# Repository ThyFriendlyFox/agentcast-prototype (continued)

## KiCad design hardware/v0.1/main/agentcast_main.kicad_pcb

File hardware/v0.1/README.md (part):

# Agentcast dongle v0.1

> **Archived** at commit `2c0782a`. Superseded by [v0.2](../v0.2/) (one board).
> First version. Made from the spec in
> [`docs/office-agent-dongle.md`](../../docs/office-agent-dongle.md) with the
> [Via EE Workcenter](https://github.com/ThyFriendlyFox/via).

v0.1 is two boards joined by a 10-way cable:

| Board | Folder | Size | Layers | What it does |
|---|---|---|---|---|
| Main board | [`main/`](main/) | 66 x 52.2 mm | 4 | Carries a Raspberry Pi Compute Module 5. HDMI-A out to the TV, USB-C power and flashing, boot button, 2 LEDs, mic bar socket. |
| Mic bar | [`micbar/`](micbar/) | 140 x 14 mm | 2 | 4 I2S MEMS mics on one shared clock, hardware mute switch, LIVE / MUTED / STATE LEDs. |

| Main board | Mic bar, from above | Mic bar, from below (LEDs, mic ports) |
|---|---|---|
|  |  |  |
|  |  |  |

The pictures come from `workcenter render <board> --views all --spin-frames 36`;
the mic bar's view from below adds `--views spin --spin-frames 36 --spin-tilt -125`.
Default zoom and pivot; the 0, 90, 180 and 270 degree test frames were whole.
The CM5 sockets and the USB-C receptacle use box bodies from `main/models/`
(KiCad has none).

Schematics: [`main/docs/schematic.png`](main/docs/schematic.png),
[`micbar/docs/schematic.png`](micbar/docs/schematic.png).

## Gate results

`workcenter gates` on each board, at the commit that adds this file:

| Board | ERC | DRC | SIM | EXPORT |
|---|---|---|---|---|
| main | PASS, 0 errors, 0 warnings | PASS, 0 errors, 0 unconnected, 0 parity; 4 silk warnings (HDMI and USB-C shells cross the edge, as designed) | SKIP, no deck (see Open items) | PASS, 24 Gerber files, drill, BOM, PDF |
| micbar | PASS, 0 errors, 0 warnings | PASS, 0 errors, 0 unconnected, 0 parity; 2 silk warnings (switch actuator crosses the edge) | PASS, 1 deck (`mic_live`) | PASS, Gerbers, drill, BOM, PDF |

## How it maps to the spec

| Spec requirement | v0.1 answer |
|---|---|
| HDMI dongle, the TV shows only what the dongle sends | CM5 HDMI0 to an HDMI-A receptacle (J3). A short HDMI cable goes to the TV, like a Chromecast tail. |
| Small, cheap, the cloud does the work | A CM5 module does Wi-Fi, HDMI 2.0 and I2S. The carrier has 26 parts. |
| A separate power supply, not the TV's USB port | USB-C (J4). The CM5 negotiates 5 V up to 5 A on CC1/CC2 itself (CM5 datasheet 2.12.1). |
| Mic unit separate from the dongle body, on the TV, facing the room | The mic bar is its own board on a JST SH cable. |
| All mic channels, not one cleaned channel | 4 raw 24-bit channels on 2 I2S data lanes (I2S0_SDI[0], I2S0_SDI[1]). No DSP on the bar. |
| A fixed, known mic layout | 4 mics in a line, 40.0 mm pitch, 120 mm aperture, positions in `micbar/design.py`. |
| One shared clock | The CM5's I2S0 is the only clock master. All 4 mics take the same BCLK and WS. |
| A physical mute; the indicator tied to mic power | SW1 cuts the mics' supply. The green LIVE LED runs from that supply. The red MUTED LED runs from the switch's other throw. |
| Software cannot turn the mics on in secret | No GPIO can power the mics. The clock buffers also run from the switched supply, so muted mics cannot draw power through their clock pins. |
| People see the state from anywhere in the room | 3 LEDs on the bar's front face. The STATE LED is driven by the CM5 (GPIO6) for "waiting / active". |
| TV control over HDMI-CEC | HDMI pin 13 goes to the CM5's HDMI0_CEC. |
| Recovery without IT | A BOOT button (nRPIBOOT) and USB-C data for `rpiboot` flashing. |

Not in v0.1: wired Ethernet, a camera, a backup speaker, a fan, more than
4 mics. See Open items.

## Part choices

| Ref | Part | Why |
|---|---|---|
| main J1, J2 | Hirose DF40C-100DS-0.4V | The CM5 board-to-board sockets. 1.5 mm stack height (CM5 datasheet 4.1.1). |
| main J3 | Molex 208658-1001 HDMI-A, mid-mount | In KiCad's library; its PCB-edge mark sets the board edge. |
| main J4 | HRO TYPE-C-31-M-12 | Common 16-pin USB 2.0 receptacle. |
| main U1 | ST USBLC6-2SC6 | ESD on the USB D+/D- pair. |
| main F1, D1, C3 | 0.1 A PTC, BAT54WS, 100 nF | HDMI +5V (pin 18): limits a short, blocks back-feed from the TV. |
| main J5 / micbar J1 | JST SH SM10B-SRSS-TB | 10-way cable between the boards, same pinout both ends. |
| main R1, R2 | 33 ohm | Source termination for BCLK and WS on the cable. |
| main R3, R4, R5 | 100 k | Pull-downs: SD0, SD1 (tri-stated by the mics) and MIC_LIVE. |
| micbar MK1-MK4 | TDK InvenSense ICS-43434 | I2S output, 24-bit, bottom port. In KiCad's library. Two mics share one data line (L/R). |
| micbar U1, U2 | 74LVC1G34 | Clock buffers on the switched supply. LVC inputs have Ioff, so a powered clock into an unpowered buffer is safe. |
| micbar SW1 | C&K PCM12SMTR | Slide switch for mute, right-angle, out of the top edge. |
| micbar D1, D2, D3 | 0603 LEDs green, red, amber | LIVE, MUTED, STATE, on the front face (B.Cu). Amber for STATE: a white LED (Vf near 3 V) would not light reliably from a 3.3 V GPIO (VOH min 2.9 V, datasheet Table 8). |

KiCad has no CM5 symbol and no 2 x 50 generic connector, so
[`library/gen_library.py`](library/gen_library.py) writes `CM5_J1` and
`CM5_J2` from [`library/cm5_pins.csv`](library/cm5_pins.csv). The CSV was
parsed from the CM5 datasheet pinout table (section 4.2), all 200 pins.
The same script copies KiCad's ICS-43434 with SD as tri-state.

## Pin plan (CM5)

Read from the CM5 datasheet: the GPIO alternate-function table (section 2.9)
and the pinout (section 4.2). GPIO_VREF (pin 78) is tied to CM5_3.3V, so all
GPIO are 3.3 V.

| Signal | CM5 pin | GPIO | Function | Goes to |
|---|---|---|---|---|
| MIC_BCLK | 49 | GPIO18 | I2S0_SCLK (alt a2), master | R1, J5.3 |
| MIC_WS | 26 | GPIO19 | I2S0_WS (alt a2) | R2, J5.5 |
| MIC_SD0 | 27 | GPIO20 | I2S0_SDI[0] (alt a2) | J5.6, mics 1-2 |
| MIC_SD1 | 46 | GPIO22 | I2S0_SDI[1] (alt a2) | J5.7, mics 3-4 |
| MIC_LIVE | 34 | GPIO5 | input, high = mics powered | J5.8 |
| STATE_LED | 30 | GPIO6 | output, high = LED on, about 2.7 mA | J5.9 |
| LED_nACT | 21 | - | activity LED sink, 20 mA max | D3 |
| nRPIBOOT | 93 | - | boot from USB when low | SW1 |
| CC1 / CC2 | 94 / 96 | - | USB-C PD | J4 |
| USB_P / USB_N | 105 / 103 | - | USB 2.0 (OTG ID left open: device mode for rpiboot) | J4 via U1 |
| HDMI0 TX2/TX1/TX0/CLK | 170-190 (even) | - | TMDS | J3 pins 1-12 |
| HDMI0_CEC / HOTPLUG | 151 / 153 | - | 5 V tolerant, direct to the connector | J3.13 / J3.19 |
| HDMI0_SDA / SCL | 199 / 200 | - | 5 V tolerant, 1.8 k pull-ups inside the CM5 | J3.16 / J3.15 |
| 5V | 77-87 (odd) | - | 4.75-5.25 V in | In2.Cu +5V pour |
| CM5_3.3V | 84, 86 | - | out, 600 mA total | GPIO_VREF, mic bar |

Shared-resource checks: I2S0 is one block, so SDI[0] and SDI[1] share its
BCLK and WS by construction. GPIO18-22 have no second use on this board.
Nothing off the board reaches a GPIO but the cable; every cable signal is
powered from CM5_3.3V, which is off when the CM5 is off (datasheet 4.2.1,
"Reverse voltage").

## Mic bar cable (J5 on main, J1 on the bar)

| Pin | Net | Notes |
|---|---|---|
| 1 | +3V3 | CM5_3.3V to the mute switch |
| 2, 4, 10, MP | GND | |
| 3 | BCLK | 33 ohm at the CM5 end |
| 5 | WS | 33 ohm at the CM5 end |
| 6 | SD0 | mics 1 (L), 2 (R) |
| 7 | SD1 | mics 3 (L), 4 (R) |
| 8 | MIC_LIVE | 10 k from the mics' supply, 100 k pull-down on the main board |
| 9 | STATE_LED | CM5 GPIO6 to the amber LED through 330 ohm |

## External contacts

| Board | Contact | Position (board origin top-left) | Nets |
|---|---|---|---|
| main | J3 HDMI-A | bottom edge, centre x 17.45 mm | TMDS, CEC, DDC, HPD, +5VP, GND |
| main | J4 USB-C | bottom edge, centre x 48.0 mm | +5V, CC1, CC2, USB_DP, USB_DN, GND |
| main | J5 mic bar | right edge, centre y 20.0 mm | see the cable table |
| main | SW1 BOOT | x 32.0, y 47.5 mm | nRPIBOOT, GND |
| micbar | J1 cable | bottom edge, centre x 70.0 mm | see the cable table |
| micbar | SW1 mute | top edge, centre x 70.0 mm | +3V3, MIC_VDD, MUTED |
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
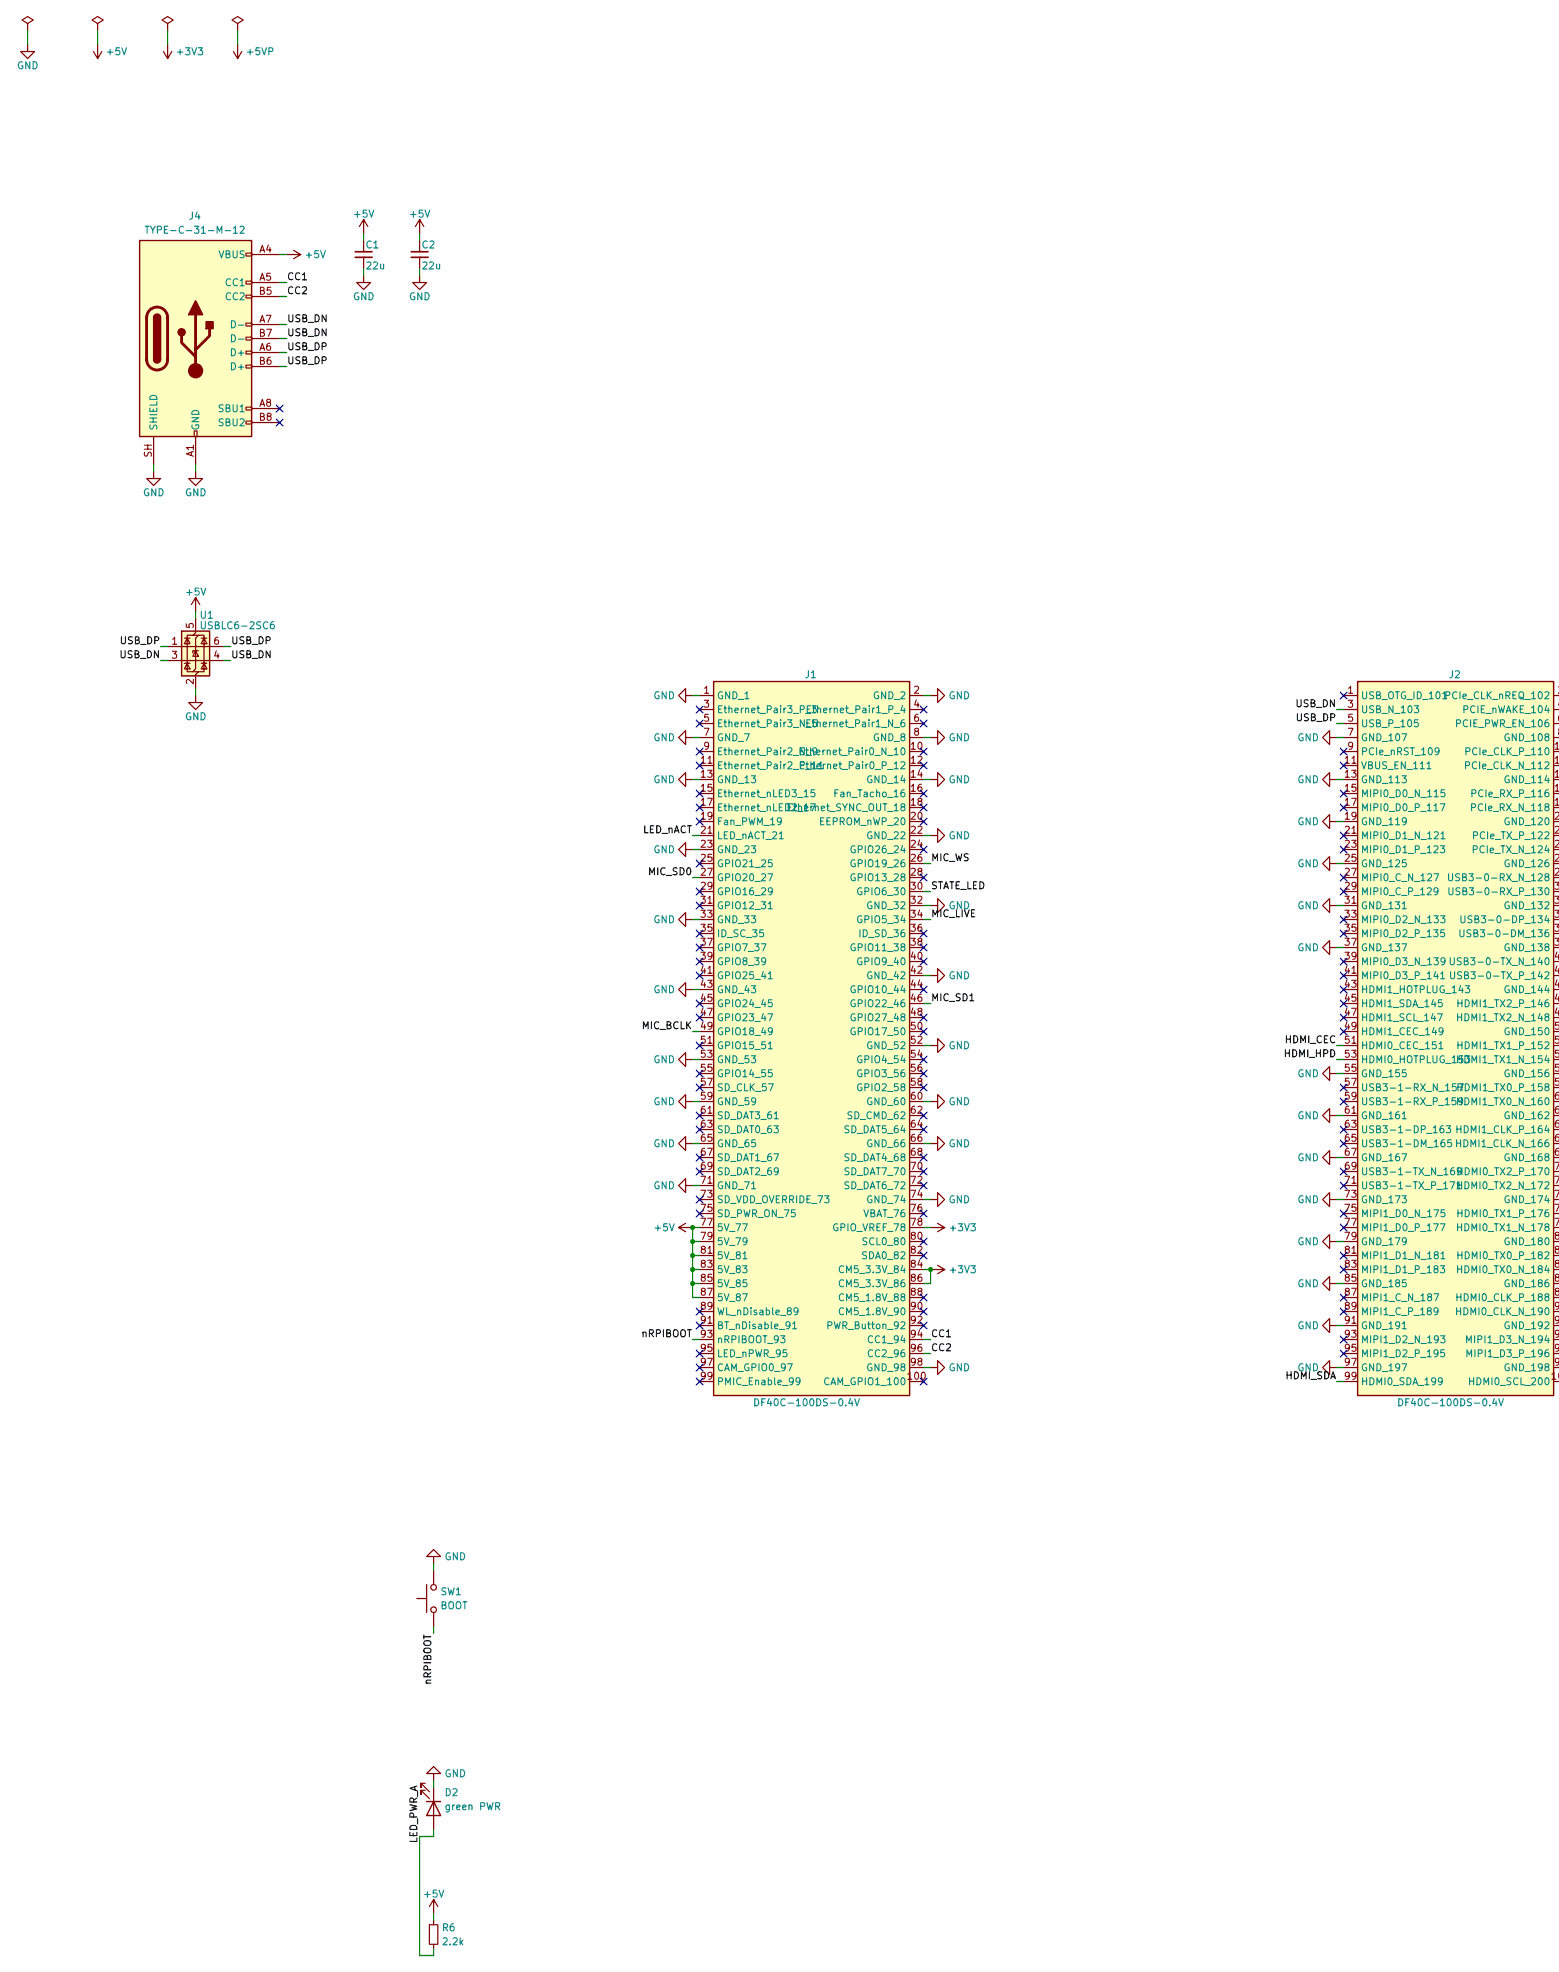
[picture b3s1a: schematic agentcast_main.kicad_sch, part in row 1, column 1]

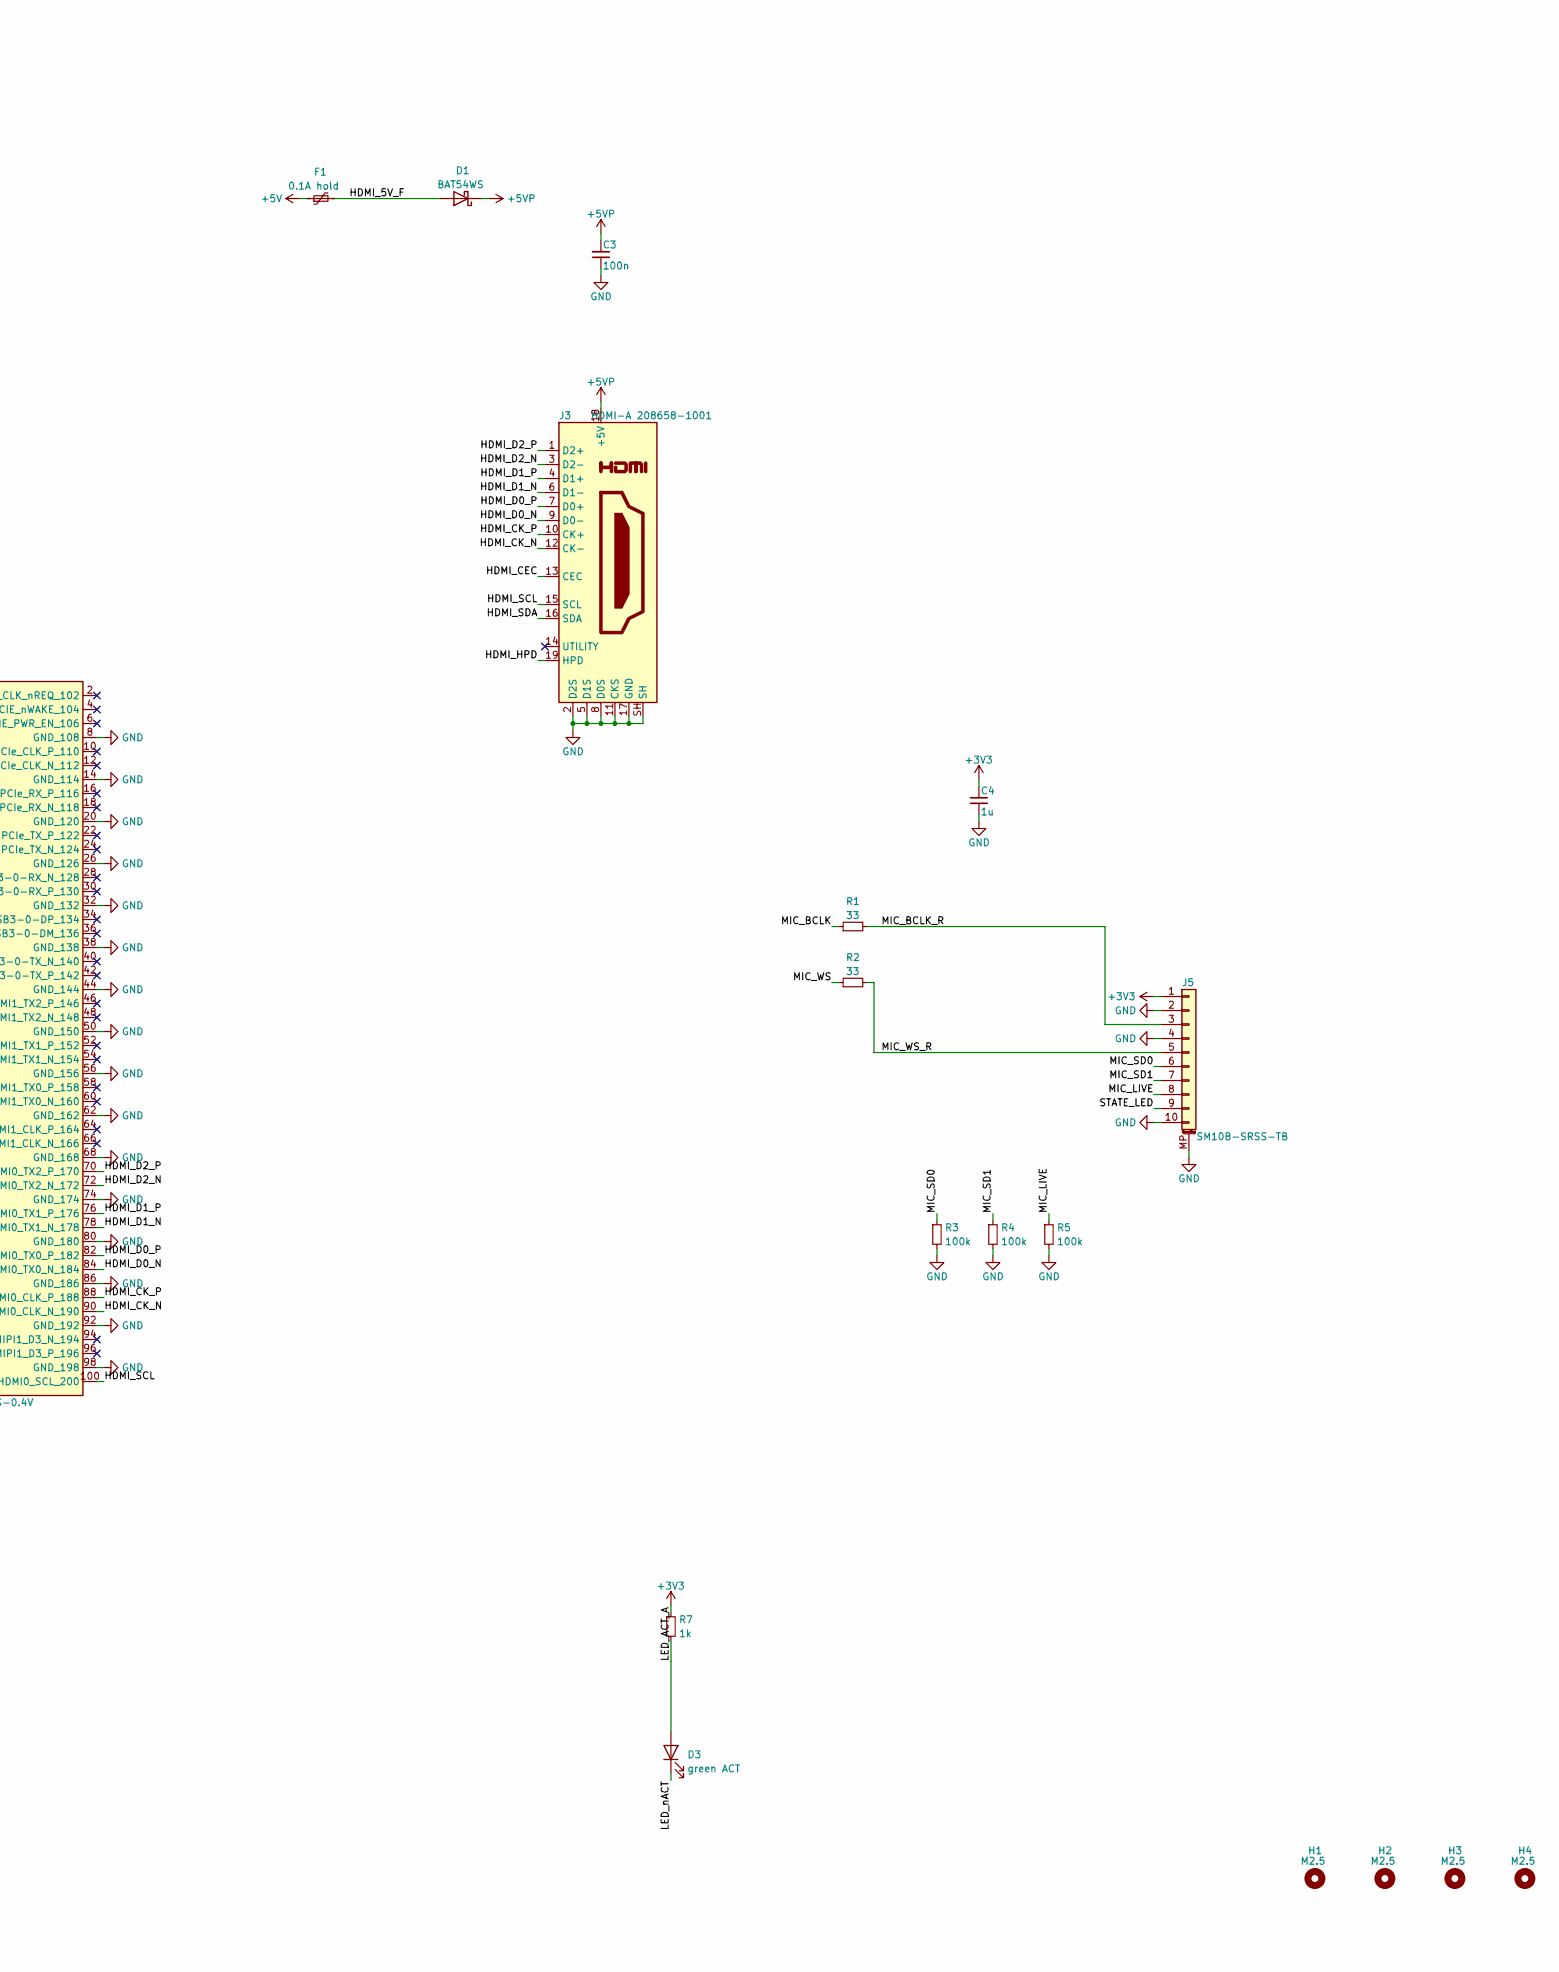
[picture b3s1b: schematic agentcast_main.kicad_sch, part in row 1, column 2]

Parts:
C1, C2: 22u; C_0805_2012Metric
C3: 100n; C_0402_1005Metric
C4: 1u; C_0402_1005Metric
D1: BAT54WS; D_SOD-323
D2: green PWR; LED_0603_1608Metric
D3: green ACT; LED_0603_1608Metric
F1: 0.1A hold; Fuse_0805_2012Metric
H1, H2, H3, H4: M2.5; MountingHole_2.7mm_M2.5
J1, J2: DF40C-100DS-0.4V; Hirose_DF40C-100DS-0.4V_2x50_P0.4mm
J3: HDMI-A 208658-1001; HDMI_A_Molex_208658-1001_Horizontal
J4: TYPE-C-31-M-12; USB_C_Receptacle_HRO_TYPE-C-31-M-12
J5: SM10B-SRSS-TB; JST_SH_SM10B-SRSS-TB_1x10-1MP_P1.00mm_Horizontal
R1, R2: 33; R_0402_1005Metric
R3, R4, R5: 100k; R_0402_1005Metric
R6: 2.2k; R_0402_1005Metric
R7: 1k; R_0402_1005Metric
SW1: BOOT; SW_SPST_TL3342
U1: USBLC6-2SC6; SOT-23-6

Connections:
+3V3: C4.1, J1.78 (GPIO_VREF_78), J1.84 (CM5_3.3V_84), J1.86 (CM5_3.3V_86), J5.1, R7.1
+5V: C1.1, C2.1, F1.1, J1.77 (5V_77), J1.79 (5V_79), J1.81 (5V_81), J1.83 (5V_83), J1.85 (5V_85), J1.87 (5V_87), J4.A4 (VBUS), J4.A9 (VBUS), J4.B4 (VBUS), J4.B9 (VBUS), R6.1, U1.5 (VBUS)
+5VP: C3.1, D1.1 (K), J3.18 (+5V)
/CC1: J1.94 (CC1_94), J4.A5 (CC1)
/CC2: J1.96 (CC2_96), J4.B5 (CC2)
/HDMI_5V_F: D1.2 (A), F1.2
/HDMI_CEC: J2.51 (HDMI0_CEC_151), J3.13 (CEC)
/HDMI_CK_N: J2.90 (HDMI0_CLK_N_190), J3.12 (CK-)
/HDMI_CK_P: J2.88 (HDMI0_CLK_P_188), J3.10 (CK+)
/HDMI_D0_N: J2.84 (HDMI0_TX0_N_184), J3.9 (D0-)
/HDMI_D0_P: J2.82 (HDMI0_TX0_P_182), J3.7 (D0+)
/HDMI_D1_N: J2.78 (HDMI0_TX1_N_178), J3.6 (D1-)
/HDMI_D1_P: J2.76 (HDMI0_TX1_P_176), J3.4 (D1+)
/HDMI_D2_N: J2.72 (HDMI0_TX2_N_172), J3.3 (D2-)
/HDMI_D2_P: J2.70 (HDMI0_TX2_P_170), J3.1 (D2+)
/HDMI_HPD: J2.53 (HDMI0_HOTPLUG_153), J3.19 (HPD)
/HDMI_SCL: J2.100 (HDMI0_SCL_200), J3.15 (SCL)
/HDMI_SDA: J2.99 (HDMI0_SDA_199), J3.16 (SDA)
/LED_ACT_A: D3.2 (A), R7.2
/LED_PWR_A: D2.2 (A), R6.2
/LED_nACT: D3.1 (K), J1.21 (LED_nACT_21)
/MIC_BCLK: J1.49 (GPIO18_49), R1.1
/MIC_BCLK_R: J5.3, R1.2
/MIC_LIVE: J1.34 (GPIO5_34), J5.8, R5.1
/MIC_SD0: J1.27 (GPIO20_27), J5.6, R3.1
/MIC_SD1: J1.46 (GPIO22_46), J5.7, R4.1
/MIC_WS: J1.26 (GPIO19_26), R2.1
/MIC_WS_R: J5.5, R2.2
/STATE_LED: J1.30 (GPIO6_30), J5.9
/USB_DN: J2.3 (USB_N_103), J4.A7 (D-), J4.B7 (D-), U1.3 (I/O2), U1.4 (I/O2)
/USB_DP: J2.5 (USB_P_105), J4.A6 (D+), J4.B6 (D+), U1.1 (I/O1), U1.6 (I/O1)
/nRPIBOOT: J1.93 (nRPIBOOT_93), SW1.1
GND: C1.2, C2.2, C3.2, C4.2, D2.1 (K), J1.1 (GND_1), J1.2 (GND_2), J1.7 (GND_7), J1.8 (GND_8), J1.13 (GND_13), J1.14 (GND_14), J1.22 (GND_22), J1.23 (GND_23), J1.32 (GND_32), J1.33 (GND_33), J1.42 (GND_42), J1.43 (GND_43), J1.52 (GND_52), J1.53 (GND_53), J1.59 (GND_59), J1.60 (GND_60), J1.65 (GND_65), J1.66 (GND_66), J1.71 (GND_71), J1.74 (GND_74), J1.98 (GND_98), J2.7 (GND_107), J2.8 (GND_108), J2.13 (GND_113), J2.14 (GND_114), J2.19 (GND_119), J2.20 (GND_120), J2.25 (GND_125), J2.26 (GND_126), J2.31 (GND_131), J2.32 (GND_132), J2.37 (GND_137), J2.38 (GND_138), J2.44 (GND_144), J2.50 (GND_150), J2.55 (GND_155), J2.56 (GND_156), J2.61 (GND_161), J2.62 (GND_162), J2.67 (GND_167), J2.68 (GND_168), J2.73 (GND_173), J2.74 (GND_174), J2.79 (GND_179), J2.80 (GND_180), J2.85 (GND_185), J2.86 (GND_186), J2.91 (GND_191), J2.92 (GND_192), J2.97 (GND_197), J2.98 (GND_198), J3.2 (D2S), J3.5 (D1S), J3.8 (D0S), J3.11 (CKS), J3.17 (GND), J3.SH, J4.A1 (GND), J4.A12 (GND), J4.B1 (GND), J4.B12 (GND), J4.SH (SHIELD), J5.2, J5.4, J5.10, J5.MP (MountPin), R3.2, R4.2, R5.2, SW1.2, U1.2 (GND)

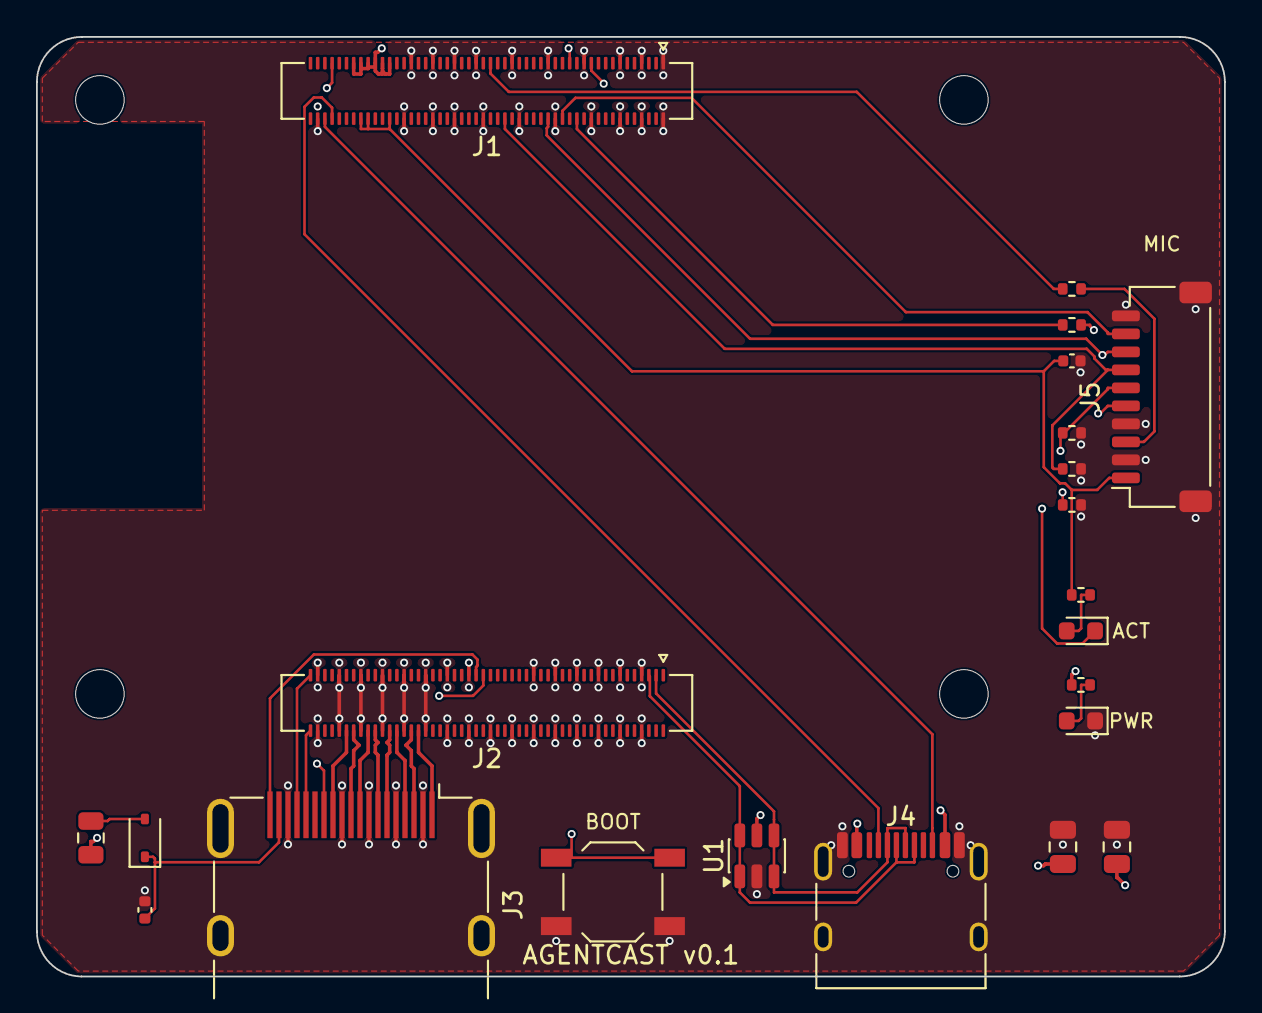
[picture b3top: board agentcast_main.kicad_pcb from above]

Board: 4 copper layers, 66.0 x 52.2 mm, 26 parts (0 on the bottom side), 33 nets.

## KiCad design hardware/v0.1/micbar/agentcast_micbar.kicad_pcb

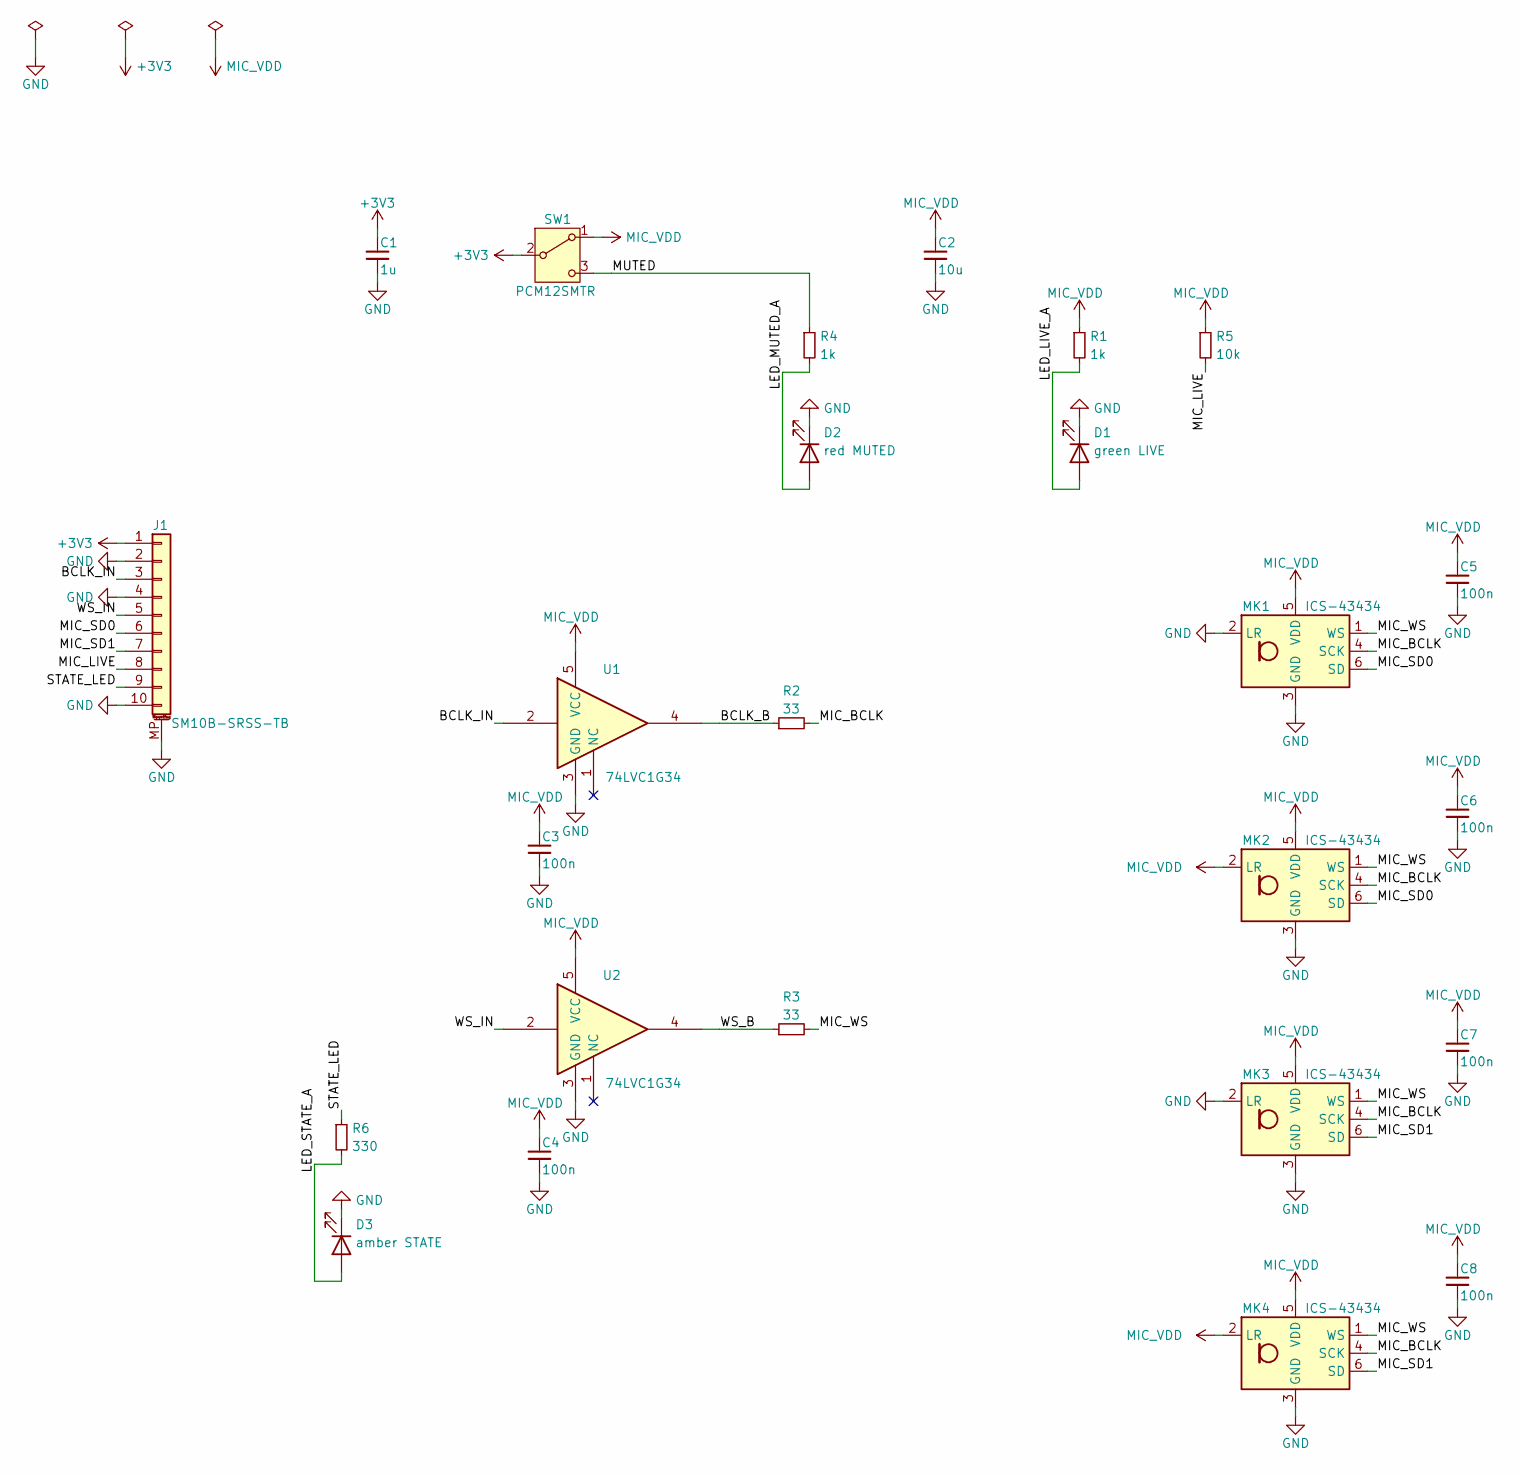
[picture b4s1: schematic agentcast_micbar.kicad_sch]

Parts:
C1: 1u; C_0402_1005Metric
C2: 10u; C_0603_1608Metric
C3, C4, C5, C6, C7, C8: 100n; C_0402_1005Metric
D1: green LIVE; LED_0603_1608Metric
D2: red MUTED; LED_0603_1608Metric
D3: amber STATE; LED_0603_1608Metric
J1: SM10B-SRSS-TB; JST_SH_SM10B-SRSS-TB_1x10-1MP_P1.00mm_Horizontal
MK1, MK2, MK3, MK4: ICS-43434; InvenSense_ICS-43434-6_3.5x2.65mm
R1, R4: 1k; R_0402_1005Metric
R2, R3: 33; R_0402_1005Metric
R5: 10k; R_0402_1005Metric
R6: 330; R_0402_1005Metric
SW1: PCM12SMTR; SW_SPDT_PCM12
U1, U2: 74LVC1G34; SOT-353_SC-70-5

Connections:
+3V3: C1.1, J1.1, SW1.2 (B)
/BCLK_B: R2.1, U1.4
/BCLK_IN: J1.3, U1.2
/LED_LIVE_A: D1.2 (A), R1.2
/LED_MUTED_A: D2.2 (A), R4.2
/LED_STATE_A: D3.2 (A), R6.2
/MIC_BCLK: MK1.4 (SCK), MK2.4 (SCK), MK3.4 (SCK), MK4.4 (SCK), R2.2
/MIC_LIVE: J1.8, R5.2
/MIC_SD0: J1.6, MK1.6 (SD), MK2.6 (SD)
/MIC_SD1: J1.7, MK3.6 (SD), MK4.6 (SD)
/MIC_WS: MK1.1 (WS), MK2.1 (WS), MK3.1 (WS), MK4.1 (WS), R3.2
/MUTED: R4.1, SW1.3 (C)
/STATE_LED: J1.9, R6.1
/WS_B: R3.1, U2.4
/WS_IN: J1.5, U2.2
GND: C1.2, C2.2, C3.2, C4.2, C5.2, C6.2, C7.2, C8.2, D1.1 (K), D2.1 (K), D3.1 (K), J1.2, J1.4, J1.10, J1.MP (MountPin), MK1.2 (LR), MK1.3 (GND), MK2.3 (GND), MK3.2 (LR), MK3.3 (GND), MK4.3 (GND), U1.3 (GND), U2.3 (GND)
MIC_VDD: C2.1, C3.1, C4.1, C5.1, C6.1, C7.1, C8.1, MK1.5 (VDD), MK2.2 (LR), MK2.5 (VDD), MK3.5 (VDD), MK4.2 (LR), MK4.5 (VDD), R1.1, R5.1, SW1.1 (A), U1.5 (VCC), U2.5 (VCC)

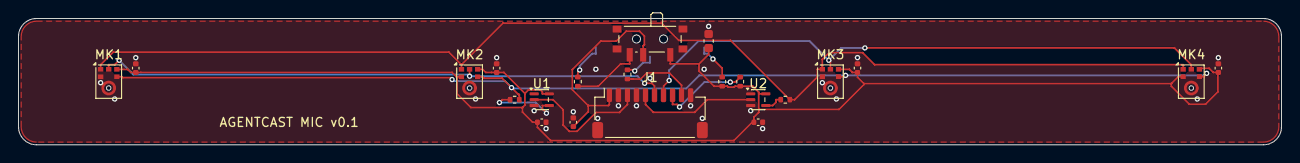
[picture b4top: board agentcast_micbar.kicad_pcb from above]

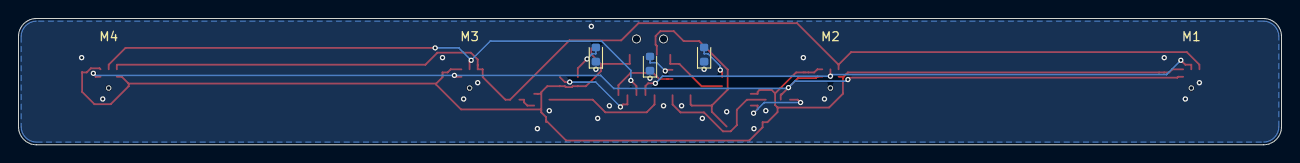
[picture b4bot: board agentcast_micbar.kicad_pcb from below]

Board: 2 copper layers, 140.0 x 14.0 mm, 25 parts (3 on the bottom side), 17 nets.

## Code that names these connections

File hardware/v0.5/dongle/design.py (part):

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
Voltage domains: +5V (USB-C), +3V3 (P4 IO banks 0/4/5 and LP, C6, USB), VDD_HP (P4 core, ~1.1 V from
U5 under the P4's own control, Espressif hardware design guidelines Fig. 5), +1V8 (LT8912B and P4
IO bank 6, GPIO49-54, which talks to it: the LT8912B's I2C and I2S pins are 1.8 V CMOS, LT8912B
datasheet Table 6.2.1), MIC_3V3 / MIC_1V8 (switched by the mute switch).

Area rules (P3 step 4):
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# ESP32-P4 pin -> net (pin plan, README). Unlisted GPIOs are left open.
P4_NETS = {
    9: "+3V3", 21: "+3V3", 62: "+3V3", 85: "+3V3", 51: "+3V3", 75: "+3V3", 77: "+3V3", 101: "+3V3", 102: "+3V3",
    96: "+1V8",  # VDD_IO_6: GPIO49-54 at 1.8 V for the LT8912B and the mic
    26: "VDD_HP", 54: "VDD_HP", 76: "VDD_HP", 91: "VDD_HP",
    30: "VDDO_FLASH", 71: "VDDO_FLASH",  # flash LDO out (3.3 V default) -> flash IO and flash VCC
    59: "VDDO_PSRAM", 67: "VDDO_PSRAM", 72: "VDDO_PSRAM",  # PSRAM LDO out -> in-package PSRAM IO
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    27: "FLASH_CS", 28: "FLASH_Q", 29: "FLASH_WP", 31: "FLASH_HOLD", 32: "FLASH_CK", 33: "FLASH_D",
    34: "DSI_REXT", 35: "DSI_D1_P", 36: "DSI_D1_N", 37: "DSI_CK_N", 38: "DSI_CK_P", 39: "DSI_D0_P", 40: "DSI_D0_N",
    49: "USB_HS_DN", 50: "USB_HS_DP",
    17: "C6_EN",  # GPIO16, open drain
    18: "LT_RST_N",  # GPIO17, open drain, pulled to +1V8
    19: "SDIO_CLK", 20: "SDIO_CMD", 22: "SDIO_D0", 23: "SDIO_D1", 24: "SDIO_D2", 25: "SDIO_D3",  # GPIO18-23
    52: "USB_FS_DN", 53: "USB_FS_DP",  # GPIO24/25: USB serial/JTAG
    66: "BOOT",  # GPIO35 strapping: low at reset = download mode
    68: "GPIO36_PU",  # GPIO36 strapping, held high
    # Spread over free pins, every other one, toward what each drives: a run of neighbouring
    # signal pins at 0.35 mm pitch leaves no room for their vias (README, pin plan).
    11: "C6_RXD",  # GPIO10: P4 UART TX -> C6 RXD0 (flashing the C6 from the P4)
    13: "C6_TXD",  # GPIO12
    15: "C6_BOOT",  # GPIO14: C6 GPIO9 strap, open drain
    56: "MIC_LIVE",  # GPIO27
    58: "STATE_LED",  # GPIO29
    61: "DDC_SDA_3V3", 63: "DDC_SCL_3V3",  # GPIO31/32
    88: "HDMI_CEC",  # GPIO46, open drain
    92: "LT_SDA", 93: "LT_SCL", 94: "I2S_BCLK", 95: "I2S_WS", 97: "I2S_DOUT", 98: "I2S_DIN",  # GPIO49-54
    105: "GND",
}  # fmt: skip

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    13: "HDMI_CEC", 15: "DDC_SCL", 16: "DDC_SDA", 18: "+5VP", 19: "HDMI_HPD",
}  # fmt: skip

# C6 module pin -> net (ESP32-C6 datasheet IO MUX: SDIO CMD GPIO18, CLK 19, DATA0-3 GPIO20-23).
C6_NETS = {
    3: "+3V3", 8: "C6_EN", 22: "C6_IO8", 23: "C6_BOOT",
    24: "SDIO_CMD_C6", 25: "SDIO_CLK_C6", 26: "SDIO_D0_C6", 27: "SDIO_D1_C6", 28: "SDIO_D2_C6", 29: "SDIO_D3_C6",
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    d.flagged_nets = ["GND", "+5V", "+3V3", "VDD_HP", "MIC_3V3", "VDDO_FLASH"]
    d.check_pulls = True
    d.defined_nets = {
        "C6_IO8": "10k pull-up R31 to +3V3 (C6 strap: GPIO8 high)",
        "EN_DCDC": "driven by the ESP32-P4's own power control (HDG 1.3.2); 0 V until firmware runs",
        "FLASH_CK": "driven by the ESP32-P4's dedicated FLASH_CK output (datasheet pin 32)",
        "MIC_BCLK": "driven by U13's output through the 33 ohm series resistor",
        "MIC_WS": "driven by U14's output through the 33 ohm series resistor",
        "MUTED": "held low through the MUTED LED's resistor and the LED while SW2 is in LIVE",
        "I2S_BCLK": "driven by the ESP32-P4's I2S (GPIO51); U13 has Ioff while MIC_1V8 is off",
        "I2S_WS": "driven by the ESP32-P4's I2S (GPIO52); U14 has Ioff while MIC_1V8 is off",
    }

    def add(ref, sym, value, fp, at, nets, rot=0, layer="F.Cu"):
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    C("1u", (cx + 7.4, cy + 6.3), "VDDO_PSRAM", rot=90)
    C("1u", (cx - 1.5, cy + 6.3), "VDD_MIPI")
    C("1u", (cx + 4.0, cy - 7.2), "VDDO_4")
    R("4.02k", (cx - 1.87, cy + 1.87), "DSI_REXT", "GND")  # DSI PHY reference (pin 34), under U1 between its EP vias
    # Core supply: TLV62569 per HDG Fig. 5 (chip revision v3.0 and later).
    add("U5", "Regulator_Switching:TLV62569DBV", "TLV62569DBV", SOT235, (cx + 8.0, 3.2),
        {"4": "+3V3", "1": "EN_DCDC", "3": "SW_HP", "2": "GND", "5": "FB_DCDC"}, rot=90)  # fmt: skip
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    add("SW1", "Switch:SW_Push", "BOOT", "Button_Switch_SMD:SW_SPST_B3U-1000P", (cx - 9.5, 3.0), {"1": "BOOT", "2": "GND"}, layer="B.Cu")
    add("SW3", "Switch:SW_Push", "RESET", "Button_Switch_SMD:SW_SPST_B3U-1000P", (cx - 9.5, 7.0), {"1": "CHIP_PU", "2": "GND"}, layer="B.Cu")
    R("10k", (cx - 6.2, cy - 8.0), "+3V3", "BOOT", rot=90)
    R("10k", (cx - 7.4, cy - 8.0), "+3V3", "GPIO36_PU", rot=90)
    # Flash, 16 MB quad SPI, on the top face under the P4's flash pins, turned so its near row runs in
    # their order (VCC, HOLD, CK, D): the bus stays on F.Cu, no vias in the P4's busiest corner. On VDDO_FLASH (3.3 V default, HDG Table 1); CS pulled up (HDG 1.3.4).
    add("U4", "Memory_Flash:W25Q128JVP", "W25Q128JVPIQ", "Package_SON:WSON-8-1EP_6x5mm_P1.27mm_EP3.4x4.3mm",
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    for dx, dy, rot in ((-3.6, -1.0, 90), (-3.6, 1.0, 90), (3.6, -2.0, 90), (3.6, 0.8, 90), (0.0, -3.6, 0), (-1.8, 3.6, 0), (1.8, 3.6, 0)):
        C("100n", (ux + dx, uy + dy), "+1V8", rot=rot)
    C("10u", (ux - 2.0, uy - 6.0), "+1V8", layer="F.Cu")
    R("6.04k", (ux + 3.0, uy + 6.2), "LT_R6K", "GND", layer="F.Cu")  # LT8912B pin 13: external 6K
    C("2.2n", (ux + 2.4, uy - 6.0), "LT_LPF", layer="F.Cu")  # pin 35: 2 nF loop filter
    # LT8912B crystal: the datasheet asks for one on XTALI/XTALO but gives no frequency (README).
    add("Y2", "Device:Crystal_GND24", "25MHz (confirm)", XTAL, (ux - 7.4, uy), {"1": "LT_XI", "3": "LT_XO", "2": "GND", "4": "GND"}, rot=90)
    C("12p", (ux - 6.8, uy - 3.0), "LT_XI", layer="F.Cu")
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    R("18k", (72.5, 19.0), "HDMI_HPD", "LT_HPD", rot=90)
    R("10k", (73.7, 19.0), "LT_HPD", "GND", rot=90)
    # DDC (EDID) at 5 V to the P4's 3.3 V I2C through BSS138 shifters; source pull-ups 1.8k to +5VP.
    for k, (line, gpio) in enumerate((("DDC_SDA", "DDC_SDA_3V3"), ("DDC_SCL", "DDC_SCL_3V3"))):
        add(f"Q{k + 1}", "Transistor_FET:BSS138", "BSS138", SOT23, (71.5 - 3.0 * k, 4.5),
            {"1": "+3V3", "2": gpio, "3": line}, rot=90, layer="B.Cu")  # fmt: skip
        R("1.8k", (71.5 - 3.0 * k, 7.6), "+5VP", line, rot=90)
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
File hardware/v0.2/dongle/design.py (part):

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# table. Every other pin is left open, as the datasheet allows (section 4.2).
CM5_NETS = {
    21: "LED_nACT",
    26: "MIC_WS",  # GPIO19, I2S0_WS (a2)
    27: "MIC_SD0",  # GPIO20, I2S0_SDI[0] (a2)
    30: "STATE_LED",  # GPIO6, output
    34: "MIC_LIVE",  # GPIO5, input
    49: "MIC_BCLK",  # GPIO18, I2S0_SCLK (a2)
    77: "+5V",
    79: "+5V",
    81: "+5V",
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    d.flagged_nets = ["GND", "+5V", "+3V3", "MIC_VDD"]  # +5VP is driven by U2's output
    d.check_pulls = True
    d.defined_nets = {
        "nRPIBOOT": "CM5 pin 93: internal 10k pull-up to CM5_3.3V (CM5 datasheet section 4.2)",
        "HDMI_SDA": "CM5 pin 199: internal 1.8k pull-up (CM5 datasheet section 4.2)",
        "HDMI_SCL": "CM5 pin 200: internal 1.8k pull-up (CM5 datasheet section 4.2)",
        "MIC_BCLK": "driven by U5's output through the 33 ohm series resistor R1",
        "MIC_WS": "driven by U6's output through the 33 ohm series resistor R2",
        "MUTED": "held low through R14 and D2 to GND while SW2 is in LIVE",
        "I2S_BCLK": "driven by the CM5's I2S0_SCLK (GPIO18); U5 has Ioff while MIC_VDD is off",
        "I2S_WS": "driven by the CM5's I2S0_WS (GPIO19); U6 has Ioff while MIC_VDD is off",
    }
    # Labels for the nets that cross the sheet between the CM5 sockets and the other blocks.
    d.sch_label_nets = (
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
    table = cm5_pins()
    nets_of = dict(CM5_NETS)
    nets_of[26], nets_of[49] = "I2S_WS", "I2S_BCLK"  # GPIO19, GPIO18: into the clock buffers
    sockets = (("J1", "CM5_J1", 1, J1_AT), ("J2", "CM5_J2", 101, J2_AT))
    for ref, sym, first, at in sockets:
        nets = {}
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    small("R5", "Device:R_Small", "100k", R0402, (25.5, 20.0), {"1": "MIC_LIVE", "2": "GND"}, rot=90)

    # On-board mic: ICS-43434, left channel of I2S0_SDI[0]. Its clocks come through buffers on
    # MIC_VDD (74LVC Ioff), so a muted mic gets no power through its clock pins.
    d.add("MK1", "Agentcast:ICS-43434_TS", "ICS-43434", "Sensor_Audio:InvenSense_ICS-43434-6_3.5x2.65mm",
          sch_at=(0, 0), pcb_at=MIC_AT,
          nets={"1": "MIC_WS", "2": "GND", "3": "GND", "4": "MIC_BCLK", "5": "MIC_VDD", "6": "MIC_SD0"})  # fmt: skip
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
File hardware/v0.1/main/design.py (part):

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# table. Every other pin is left open, as the datasheet allows (section 4.2).
CM5_NETS = {
    21: "LED_nACT",
    26: "MIC_WS",  # GPIO19, I2S0_WS (a2)
    27: "MIC_SD0",  # GPIO20, I2S0_SDI[0] (a2)
    30: "STATE_LED",  # GPIO6, output
    34: "MIC_LIVE",  # GPIO5, input
    46: "MIC_SD1",  # GPIO22, I2S0_SDI[1] (a2)
    49: "MIC_BCLK",  # GPIO18, I2S0_SCLK (a2)
    77: "+5V",
    79: "+5V",
    81: "+5V",
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    d.flagged_nets = ["GND", "+5V", "+3V3", "+5VP"]
    d.check_pulls = True
    d.defined_nets = {
        "nRPIBOOT": "CM5 pin 93: internal 10k pull-up to CM5_3.3V (CM5 datasheet section 4.2)",
        "HDMI_SDA": "CM5 pin 199: internal 1.8k pull-up (CM5 datasheet section 4.2)",
        "HDMI_SCL": "CM5 pin 200: internal 1.8k pull-up (CM5 datasheet section 4.2)",
    }
    # Labels for the nets that cross the sheet between the two CM5 sockets and the connectors.
    d.sch_label_nets = (
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
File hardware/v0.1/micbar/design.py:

"""Agentcast dongle v0.1, mic bar: four I2S MEMS microphones on a bar that sits on the TV.

The bar joins the main board by a 10-way JST SH cable (same pinout on both ends). The CM5's I2S0
is the clock master: one BCLK and one WS for all four mics, so every channel shares one clock.
Two data lanes carry two mics each (ICS-43434 L/R select).

    workcenter design design.py --route     # from this folder

Board: 140 x 14 mm, 2 layers. The bar stands on its long edge facing the room: the parts sit on
F.Cu (the back), the mics' bottom ports open through the board to B.Cu (the front), and the three
LEDs sit on B.Cu so the room sees them. The mute slide switch sticks out of the top edge.

Mute (spec "Consent, privacy and trust"): SW1 switches the mics' supply. In "live" it feeds
MIC_VDD; in "mute" it feeds the red LED and MIC_VDD has no source. The green LIVE LED runs from
MIC_VDD itself, so it is lit exactly when the mics have power; no software can change that. The
clock buffers U1 and U2 run from MIC_VDD too: with the mics off, the CM5's clocks stop at the
buffers' inputs (74LVC Ioff) and cannot feed the mics through their input clamp diodes.

Area rules (P3 step 4): no keep-out. Each mic's sound hole is a non-plated hole in its footprint;
the pours keep the edge clearance from it.
"""

from __future__ import annotations

import uuid
from pathlib import Path

import kicadgen

BX, BY = 100.0, 100.0
W, H = 140.0, 14.0
MIC_X = [BX + 10.0, BX + 50.0, BX + 90.0, BX + 130.0]  # 40 mm pitch, 120 mm aperture
MIC_Y = BY + 7.0

# Schematic layout (P24): ref -> (x, y, angle), 2.54 mm steps, A3 sheet.
SCHEMATIC = {
    "J1": (38.1, 101.6, 0),
    "C1": (68.58, 50.8, 0),
    "SW1": (93.98, 50.8, 0),
    "R4": (129.54, 63.5, 0),
    "D2": (129.54, 78.74, 270),
    "C2": (147.32, 50.8, 0),
    "R1": (167.64, 63.5, 0),
    "D1": (167.64, 78.74, 270),
    "R5": (185.42, 63.5, 0),
    "U1": (101.6, 116.84, 0),
    "C3": (91.44, 134.62, 0),
    "U2": (101.6, 160.02, 0),
    "C4": (91.44, 177.8, 0),
    "R2": (127.0, 116.84, 90),
    "R3": (127.0, 160.02, 90),
    "MK1": (198.12, 106.68, 0),
    "C5": (220.98, 96.52, 0),
    "MK2": (198.12, 139.7, 0),
    "C6": (220.98, 129.54, 0),
    "MK3": (198.12, 172.72, 0),
    "C7": (220.98, 162.56, 0),
    "MK4": (198.12, 205.74, 0),
    "C8": (220.98, 195.58, 0),
    "R6": (63.5, 175.26, 0),
    "D3": (63.5, 190.5, 270),
}


def build() -> kicadgen.Design:
    d = kicadgen.Design(name="agentcast_micbar", namespace=uuid.UUID("2c9d41e0-6a77-4f5b-8f0e-3b5a1d7c9e21"))
    d.sheet = "A3"
    d.symbol_dirs = {"Agentcast": Path(__file__).resolve().parent.parent / "library" / "agentcast.kicad_sym"}
    d.sch_wires = True
    d.outline = (BX, BY, BX + W, BY + H)
    d.corner_radius = 2.0
    d.track_width = 0.2
    d.clearance = 0.15
    d.edge_clearance = 0.3
    d.via_size = 0.6
    d.via_drill = 0.3
    d.power_nets = {"GND": "GND", "+3V3": "+3V3", "MIC_VDD": "VDD"}
    d.flagged_nets = ["GND", "+3V3", "MIC_VDD"]
    d.check_pulls = True
    d.defined_nets = {
        "BCLK_IN": "driven by the CM5's I2S0_SCLK through R1 on the main board; U1 has Ioff",
        "WS_IN": "driven by the CM5's I2S0_WS through R2 on the main board; U2 has Ioff",
        "MIC_SD0": "100k pull-down R3 on the main board",
        "MIC_SD1": "100k pull-down R4 on the main board",
        "MIC_BCLK": "driven by U1's output through the 33 ohm series resistor R2",
        "MIC_WS": "driven by U2's output through the 33 ohm series resistor R3",
        "MUTED": "held low through R4 and D2 to GND while SW1 is in LIVE",
    }
    d.sch_label_nets = ("MIC_BCLK", "MIC_WS", "MIC_SD0", "MIC_SD1", "BCLK_IN", "WS_IN", "MIC_LIVE", "STATE_LED")

    d.add(
        "J1",
        "Connector_Generic_MountingPin:Conn_01x10_MountingPin",
        "SM10B-SRSS-TB",
        "Connector_JST:JST_SH_SM10B-SRSS-TB_1x10-1MP_P1.00mm_Horizontal",
        sch_at=(0, 0),
        pcb_at=(BX + 70.0, BY + 10.5),
        nets={
            "1": "+3V3", "2": "GND", "3": "BCLK_IN", "4": "GND", "5": "WS_IN",
            "6": "MIC_SD0", "7": "MIC_SD1", "8": "MIC_LIVE", "9": "STATE_LED", "10": "GND", "MP": "GND",
        },
    )
    d.add("C1", "Device:C_Small", "1u", "Capacitor_SMD:C_0402_1005Metric",
          sch_at=(0, 0), pcb_at=(BX + 61.5, BY + 11.5), pcb_rot=90, nets={"1": "+3V3", "2": "GND"})  # fmt: skip
    d.add("SW1", "Switch:SW_SPDT", "PCM12SMTR", "Button_Switch_SMD:SW_SPDT_PCM12",
          sch_at=(0, 0), pcb_at=(BX + 70.0, BY + 2.6), pcb_rot=180,
          nets={"2": "+3V3", "1": "MIC_VDD", "3": "MUTED"})  # fmt: skip
    d.add("C2", "Device:C_Small", "10u", "Capacitor_SMD:C_0603_1608Metric",
          sch_at=(0, 0), pcb_at=(BX + 76.5, BY + 2.5), pcb_rot=90, nets={"1": "MIC_VDD", "2": "GND"})  # fmt: skip

    # LEDs on the front face (B.Cu): MUTED red, LIVE green (from MIC_VDD), STATE amber (CM5 GPIO6).
    d.add("R4", "Device:R_Small", "1k", "Resistor_SMD:R_0402_1005Metric",
          sch_at=(0, 0), pcb_at=(BX + 62.0, BY + 7.0), pcb_rot=90, nets={"1": "MUTED", "2": "LED_MUTED_A"})  # fmt: skip
    d.add("D2", "Device:LED", "red MUTED", "LED_SMD:LED_0603_1608Metric",
          sch_at=(0, 0), pcb_at=(BX + 64.0, BY + 4.0), pcb_layer="B.Cu", pcb_rot=90,
          nets={"2": "LED_MUTED_A", "1": "GND"})  # fmt: skip
    d.add("R1", "Device:R_Small", "1k", "Resistor_SMD:R_0402_1005Metric",
          sch_at=(0, 0), pcb_at=(BX + 78.0, BY + 7.0), pcb_rot=90, nets={"1": "MIC_VDD", "2": "LED_LIVE_A"})  # fmt: skip
    d.add("D1", "Device:LED", "green LIVE", "LED_SMD:LED_0603_1608Metric",
          sch_at=(0, 0), pcb_at=(BX + 76.0, BY + 4.0), pcb_layer="B.Cu", pcb_rot=90,
          nets={"2": "LED_LIVE_A", "1": "GND"})  # fmt: skip
    # MIC_LIVE tells the CM5 the mics have power: 10k from MIC_VDD into its 100k pull-down.
    d.add("R5", "Device:R_Small", "10k", "Resistor_SMD:R_0402_1005Metric",
          sch_at=(0, 0), pcb_at=(BX + 80.0, BY + 7.0), pcb_rot=90, nets={"1": "MIC_VDD", "2": "MIC_LIVE"})  # fmt: skip
    d.add("R6", "Device:R_Small", "330", "Resistor_SMD:R_0402_1005Metric",
          sch_at=(0, 0), pcb_at=(BX + 67.5, BY + 6.2), pcb_rot=90, nets={"1": "STATE_LED", "2": "LED_STATE_A"})  # fmt: skip
    d.add("D3", "Device:LED", "amber STATE", "LED_SMD:LED_0603_1608Metric",
          sch_at=(0, 0), pcb_at=(BX + 70.0, BY + 5.0), pcb_layer="B.Cu", pcb_rot=90,
          nets={"2": "LED_STATE_A", "1": "GND"})  # fmt: skip

    # Clock buffers, powered from MIC_VDD (see the module docstring).
    d.add("U1", "74xGxx:74LVC1G34", "74LVC1G34", "Package_TO_SOT_SMD:SOT-353_SC-70-5",
          sch_at=(0, 0), pcb_at=(BX + 58.0, BY + 9.0), nets={"2": "BCLK_IN", "4": "BCLK_B", "3": "GND", "5": "MIC_VDD"})  # fmt: skip
    d.add("C3", "Device:C_Small", "100n", "Capacitor_SMD:C_0402_1005Metric",
          sch_at=(0, 0), pcb_at=(BX + 58.0, BY + 11.5), nets={"1": "MIC_VDD", "2": "GND"})  # fmt: skip
    d.add("U2", "74xGxx:74LVC1G34", "74LVC1G34", "Package_TO_SOT_SMD:SOT-353_SC-70-5",
          sch_at=(0, 0), pcb_at=(BX + 82.0, BY + 9.0), nets={"2": "WS_IN", "4": "WS_B", "3": "GND", "5": "MIC_VDD"})  # fmt: skip
    d.add("C4", "Device:C_Small", "100n", "Capacitor_SMD:C_0402_1005Metric",
          sch_at=(0, 0), pcb_at=(BX + 82.0, BY + 11.5), nets={"1": "MIC_VDD", "2": "GND"})  # fmt: skip
    # 33 ohm series resistors at the buffer outputs damp the 120 mm clock lines.
    d.add("R2", "Device:R_Small", "33", "Resistor_SMD:R_0402_1005Metric",
          sch_at=(0, 0), pcb_at=(BX + 55.0, BY + 9.0), nets={"1": "BCLK_B", "2": "MIC_BCLK"})  # fmt: skip
    d.add("R3", "Device:R_Small", "33", "Resistor_SMD:R_0402_1005Metric",
          sch_at=(0, 0), pcb_at=(BX + 85.0, BY + 9.0), nets={"1": "WS_B", "2": "MIC_WS"})  # fmt: skip

    # Mics: MK1/MK2 share SD0 (left/right), MK3/MK4 share SD1.
    lanes = [("MIC_SD0", "GND"), ("MIC_SD0", "MIC_VDD"), ("MIC_SD1", "GND"), ("MIC_SD1", "MIC_VDD")]
    for i, (x, (sd, lr)) in enumerate(zip(MIC_X, lanes, strict=True), start=1):
        d.add(f"MK{i}", "Agentcast:ICS-43434_TS", "ICS-43434", "Sensor_Audio:InvenSense_ICS-43434-6_3.5x2.65mm",
              sch_at=(0, 0), pcb_at=(x, MIC_Y),
              nets={"1": "MIC_WS", "2": lr, "3": "GND", "4": "MIC_BCLK", "5": "MIC_VDD", "6": sd})  # fmt: skip
        d.add(f"C{4 + i}", "Device:C_Small", "100n", "Capacitor_SMD:C_0402_1005Metric",
              sch_at=(0, 0), pcb_at=(x + 3.0, MIC_Y - 1.5), pcb_rot=90, nets={"1": "MIC_VDD", "2": "GND"})  # fmt: skip

    for part in d.parts:
        if part.ref[0] in "RCD" or part.ref == "SW1":
            part.hide_ref = True
    for ref, (x, y, rot) in SCHEMATIC.items():
        part = next(p for p in d.parts if p.ref == ref)
        part.sch_at = (x, y)
        part.sch_rot = rot

    d.zone("GND", layers=("F.Cu", "B.Cu"), connect="solid")
    d.stitch_pads("GND")
    d.text("AGENTCAST MIC v0.1", BX + 30.0, BY + 11.5, "F.SilkS", 1.0, 0.15)
    for i, x in enumerate(MIC_X, start=1):
        d.text(f"M{i}", x, BY + 2.0, "B.SilkS", 1.0, 0.15)
    return d
